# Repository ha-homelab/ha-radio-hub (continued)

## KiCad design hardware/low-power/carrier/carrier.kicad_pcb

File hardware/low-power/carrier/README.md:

# LP-C0 low-voltage module carrier

<!-- MC2-CURRENT-DESIGN -->
> **Current build: [MC2 — three external antennas](../../../docs/external-antennas.md).** This page retains an earlier design or evaluation for reference. Its board images, pin maps, enclosure fit and alternative BOMs are not the current MC2 build.

**This is a routed, electrically connected prototype PCB, not a production release.** The native KiCad 10 project includes a schematic, a two-layer PCB, a machine-readable connector map, assembly data and prototype Gerbers. The board passes native ERC, DRC, the unconnected-item check and schematic parity. It has not been fabricated, populated, powered or RF-tested. No radio pairing, PoE interoperability, long-run reliability or 3 W AC energy target is established by these CAD checks.

Open [carrier.kicad_pro](carrier.kicad_pro) in KiCad 10. The ready-to-review [schematic PDF](outputs/schematic.pdf), [assembly drawing](outputs/assembly-top.svg) and [top copper drawing](outputs/board-top.svg) are generated from the native files. The [validation summary](outputs/validation/summary.json) states the actual check results. [Prototype fabrication files](outputs/prototype-gerbers.zip) are for engineering review and a first article only.

## What this board does

LP-C0 is a **160 × 100 mm, 1.6 mm, two-layer low-voltage backplane**. SC16IS752, its 3.6864 MHz crystal, its TPS3808G33 reset supervisor, bypass capacitors, pull-ups and unused-input terminations are on the board. Radios, controller modules, the radar and the regulator are wired through keyed connectors. The CPU assignment remains the existing LP-P0 firmware contract: one S3 host, H2 Thread RCP, MG24 Zigbee NCP, ZAC93, CC1101, LD2450 and BME680.

The carrier contains no Ethernet magnetics or PoE primary circuitry. An independently reviewed isolated PoE front end supplies **regulated 5 V** at J1. A separately mounted Pololu D24V22F3 at J2 generates the sole 3.3 V rail. WIZ850io at J4 supplies the Ethernet controller, PHY, magnetics and RJ45. Do not connect raw PoE pairs or a 48 V source to this PCB.

This partition is useful for a bench build with accessible, replaceable modules. It is not a finished plug-together kit: the actual S3/H2 development-board revision must be checked for pin access, regulator backfeed and UART/LED conflicts. The included [LP-M0 daughterboard](mg24-adapter/README.md) provides the exact MGM240PA22VNA3 footprint, power/ground lands and service access. One populated M0 is required per C0 hub; its PCB, assembly and cable end must be included in procurement. No undocumented DevKit header, CC1101 header or radar connector footprint is claimed to fit.

## Connectors and harnesses

[connectors.json](connectors.json) is the complete pin-by-pin wiring list. It contains actual PCB pad centres, connector rotation, voltage domain, remote signal name and verified module-pad/header positions where available. [assembly-bom.csv](assembly-bom.csv) lists populated PCB parts; [harness-bom.csv](harness-bom.csv) lists the mating housings, contacts and off-board assembly items.

The board is viewed **from the component side**, with its origin at the upper-left corner and positive Y down. Every connector's square pad is pin 1. The J3 IDC header uses odd and even columns, not a single left-to-right sequence. A cable socket viewed into its mating face is mirrored relative to the PCB. Use moulded circuit numbers and the manufacturer drawing, then continuity-test every conductor. The pin numbers in this project belong to the **carrier connector**; they are not development-board header numbers. J3 is emphatically **not a Raspberry Pi header**.

- J1: 2-position JST XH, isolated 5 V input and return.
- J2: 3-position JST XH, buck VIN = fused 5 V, GND, buck VOUT = 3.3 V. Check this order before power.
- J3: 40-position keyed Würth IDC, S3 GPIO, duplicate 3.3 V and ground contacts. No 5 V.
- J4: 10-position JST XH, WIZ850io power and SPI. The official WIZ850io **J2.1 is GND; J2.2/3 are 3.3 V; J2.4 is NC**. The WIZ header J2 is distinct from carrier J2.
- J5: 7-position JST XH, H2 power, UART, EN and BOOT. EN/BOOT are open-drain controls with external pull-ups.
- J6: 6-position JST XH, MG24 power and UART with RTS/CTS.
- J7: 8-position JST XH, CC1101 power, SPI and GDO0/GDO2. GDO0 is shared open-drain TX with a 4.7 kΩ pull-up.
- J8: 5-position JST XH, ZAC93 3.3 V, both ground contacts and UART. SC16 TXA goes to ZAC93 RX; SC16 RXA receives ZAC93 TX.
- J9: 4-position JST XH, LD2450 5 V supply and 3.3 V UART. The radar is the only 5 V module on these peripheral harnesses.
- J10: JST SH STEMMA QT, 1 GND / 2 3.3 V / 3 SDA / 4 SCL. BME680 stays in a ventilated external pod. Its breakout provides the I²C pull-ups.

Use 22 AWG conductors on J1/J2 and 26 AWG on signal harnesses. The selected XH contact supports 28–22 AWG; the connector's 3 A rating is specified with 22 AWG. The selected IDC **mating socket is rated 1 A per contact**, regardless of the larger header rating. Keep SPI harnesses short: start at **100 mm maximum**, route a nearby ground return, and scope the actual edges before increasing length. This is a prototype layout constraint, not a measured signal-integrity guarantee. The 10 MHz W5500 and 4 MHz SC16 bus settings have not been validated through these cables.

## Module-side prerequisites

The required module-side wiring is described in [the LP-P0 hardware contract](../README.md). In particular:

1. Power S3/H2 modules only from the regulated 3.3 V rail after verifying that their development-board regulator and USB circuitry cannot backfeed it. Never connect another live 3.3 V supply. Isolate the S3 GPIO48 LED and UART0 USB bridge connections as required by the chosen board. Native S3 USB remains on GPIO19/20 and is not routed through J3.
2. H2 requires its documented GPIO8 pull-up and GPIO25 pull-down, EN timing and GPIO9 BOOT state. J5 does not expose those two strap pins; they must exist on the H2 module adapter. The carrier supplies EN/BOOT pull-ups and EN capacitance; account for any duplicate parts on a DevKit.
3. Use the included M0 adapter for MG24: its all-ground connection, VDD bypassing, antenna keepout, PA00 boot service, SWD PA01/PA02, reset and 3.3 V reference are part of the design. Connect C0 J6 to M0 J1 straight number-to-number. Do not add a 3.3 V pull-up to its reset pin. Flash the exact [MGM240P NCP build](../../../firmware/low-power/mg24/README.md), not an unrelated USB-dongle image.
4. ZAC93 and CC1101 connections terminate in harnesses because the physical revision and mounting dimensions of the user's boards are not verified. Check pin 1 and trace continuity at the actual board before attaching power.
5. The WIZ850io **data-only Ethernet RJ45 is not itself a PoE PD**. The separate verified front end must provide a data path and isolated 5 V; the carrier does not implement that external cable assembly.

## Power and assembly limits

F1 is Littelfuse **044901.5MR**, a 1.5 A time-delay fuse. It does not provide reverse-polarity protection, overvoltage protection or active current limiting. Use an isolated, current-limited 5 V source for first power. Start with only the external regulator, then measure J2.3 before connecting modules. The provisional continuous input criterion is **at most 1.0 A at 5 V**; re-evaluate the fuse and thermal derating against measured duty cycles. A fuse rating is not a measured current draw.

The shared 3.3 V rail uses a 0.8 mm routing class and a front copper pour; ground uses a rear pour. The SC16's small local supply escape is 0.25 mm. General signal traces are 0.25 mm, minimum clearance 0.20 mm, and routed vias are 0.8 mm with 0.4 mm drills. Copper is specified as 1 oz nominal per layer. Verify voltage at the furthest module during simultaneous radio activity; an unloaded 3.3 V reading is insufficient.

The PCB has hand-solderable 0805 passives, 1206 bulk capacitors, a TSSOP-28 UART bridge and SOT-23-6 supervisor. The JST SH connector is the finest-pitch part. Assemble low components first, inspect bridges under magnification, and measure resistance between rails before power. Three ground pads (J3.8, J4.2 and J4.9) have direct plane connections to avoid isolated thermal islands; they need more soldering heat or board preheat than the other connector pads.

The initial crystal load capacitors are 22 pF and 33 pF. Their values follow the existing design contract and remain a measured-frequency/drive-level gate. The crystal traces are short local front-layer routes reserved before global routing. Do not infer oscillator start-up margin from DRC. The SC16 64-byte receive FIFO still requires firmware stress testing with all radios active.

Mounting holes are 3.2 mm NPTH at **(5,5), (155,5), (5,95), (155,95) mm**. Use insulating M3 supports and protect the underside from conductive hardware. This hole pattern and the off-board harness layout **do not match the existing low-power enclosure mock-up**. Three support positions differ; do not print the old case expecting this board to fit. Harness bend radius, module antenna clearance, PoE isolation and BME/radar placement require an enclosure revision after a physical first article.

## Reproduce and verify

KiCad 10.0.6 was used locally. `generate.py` and `finalize.py` require the Python interpreter bundled with KiCad or a Python environment providing the matching `pcbnew`. The committed PCB is the routed result; regenerating only the schematic and placement does not recreate routing.

```sh
python3 generate.py --libraries /path/to/KiCad/SharedSupport
kicad-cli sch export netlist carrier.kicad_sch --format kicadxml -o .build/carrier.xml
java -jar /path/to/freerouting-1.9.0.jar -da -dct 0 -de .build/carrier.dsn -do .build/carrier.ses -mp 40 -mt 0
python3 finalize.py
python3 -m unittest test_contract -v
python3 validate.py --kicad-cli kicad-cli --out .build/validation
python3 export.py --kicad-cli kicad-cli
python3 validate.py --kicad-cli kicad-cli --check-hashes --out .build/recheck
```

Run from this directory. FreeRouting 1.9.0 needs a graphical display even in its command-line mode; a headless Linux reroute needs a virtual display. **CI does not need to reroute.** It checks the committed native PCB with KiCad and the independent netlist/connector validator. `-mt 0` avoids the old router's multithreaded optimization problems. `-da` disables its analytics. The intermediate DSN/SES and unrouted board live under ignored `.build/`.

Validation compares schematic-exported connectivity, native PCB pad nets and the canonical design; verifies all part positions/rotations, checks actual connector pad centres; and compares external endpoints against the independently sourced visual module atlas. Native DRC includes unconnected items and schematic parity. The script parses the JSON report as well as checking process status, because an observed KiCad CLI run returned success despite reporting errors.

No electrical violation is excluded. The reports list KiCad's default ignored non-electrical checks: missing courtyard (the four board-only mounting holes have no component courtyard), track-to-via centring, tuning geometries and unused symbol footprint filters/type metadata. There are no tuned differential pairs. The five explicitly unused SC16/supervisor output/control pins are marked with no-connect flags as required by the circuit; unused SC16 input/GPIO pins are terminated. See [NOTICE.md](NOTICE.md) for library provenance and licenses.

## Before a production order

Review the prototype Gerbers and drill map with the fabricator, then make a small first-article run. Inspect the pin-1 markings and connector fit before making cables. Validate the input fuse, rail droop, regulator temperature, oscillator frequency, reset/start-up sequence, SPI integrity, all radio traffic, antenna isolation, radar window and continuous operation. The off-board PoE front end and every module adapter need their own electrical/mechanical review. Production PCBA/test fixtures, enclosure design, RF/regulatory work and a saleable product release remain separate engineering steps.

The SHA256 manifest binds source files and exported artifacts, including the fabrication ZIP. Both C0 and M0 use descriptive `.gbr` Gerber filenames. J10 has two isolated solder hold-down tabs, represented as separate NC pins MP1/MP2; they are not extra cable contacts. The full named-pad check covers these tabs as well as numbered electrical pads.

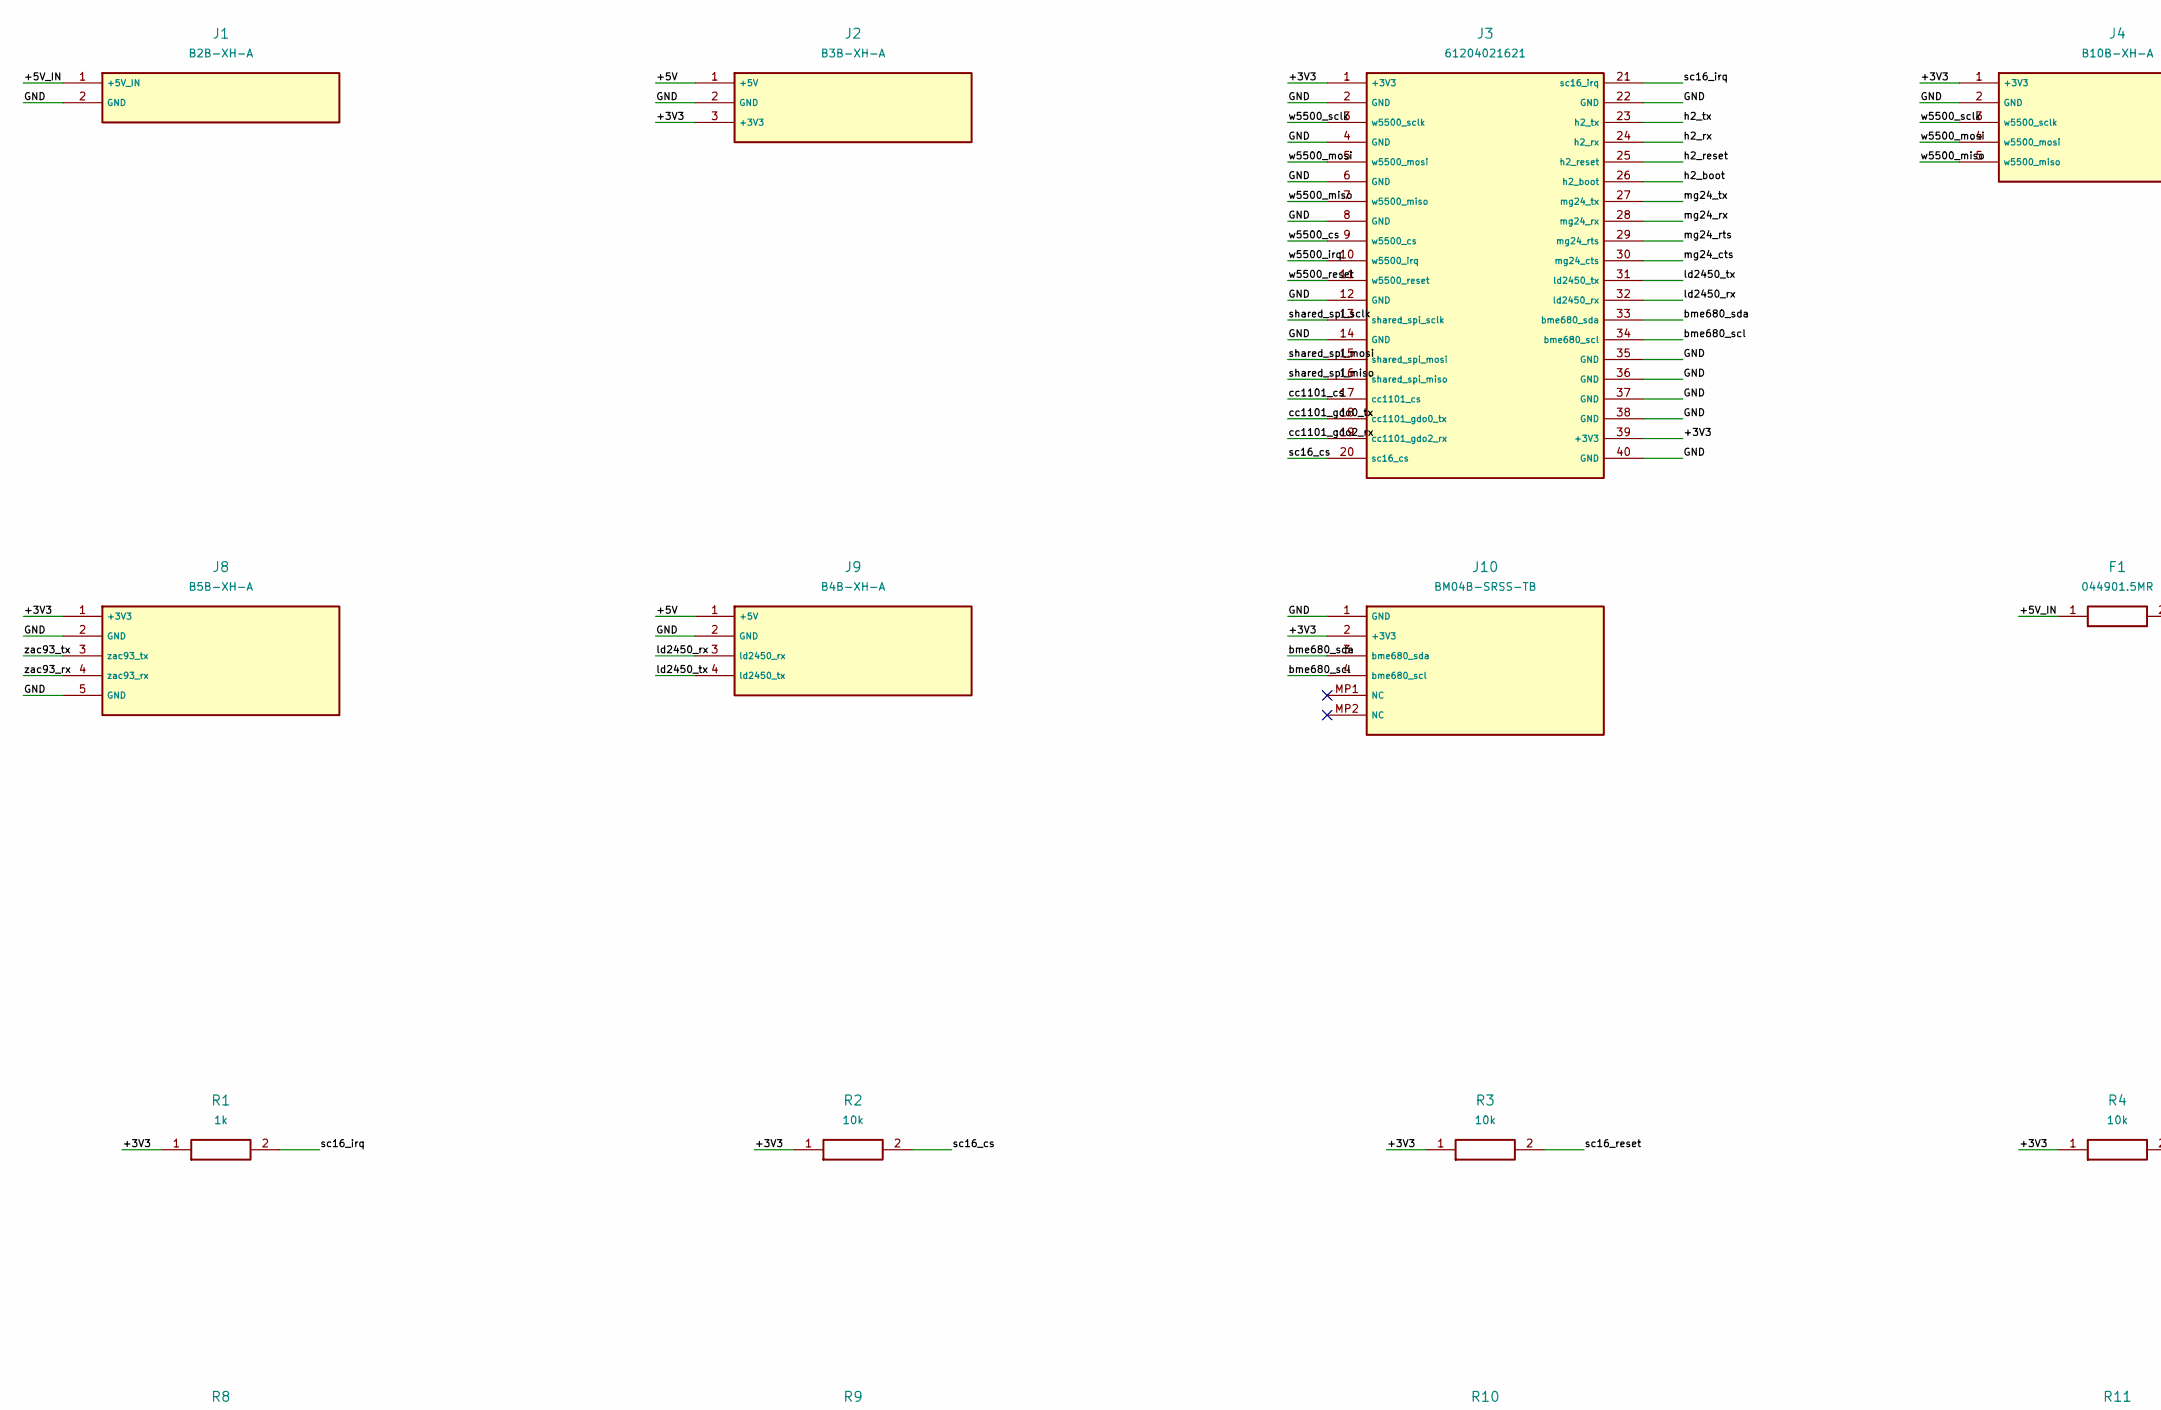
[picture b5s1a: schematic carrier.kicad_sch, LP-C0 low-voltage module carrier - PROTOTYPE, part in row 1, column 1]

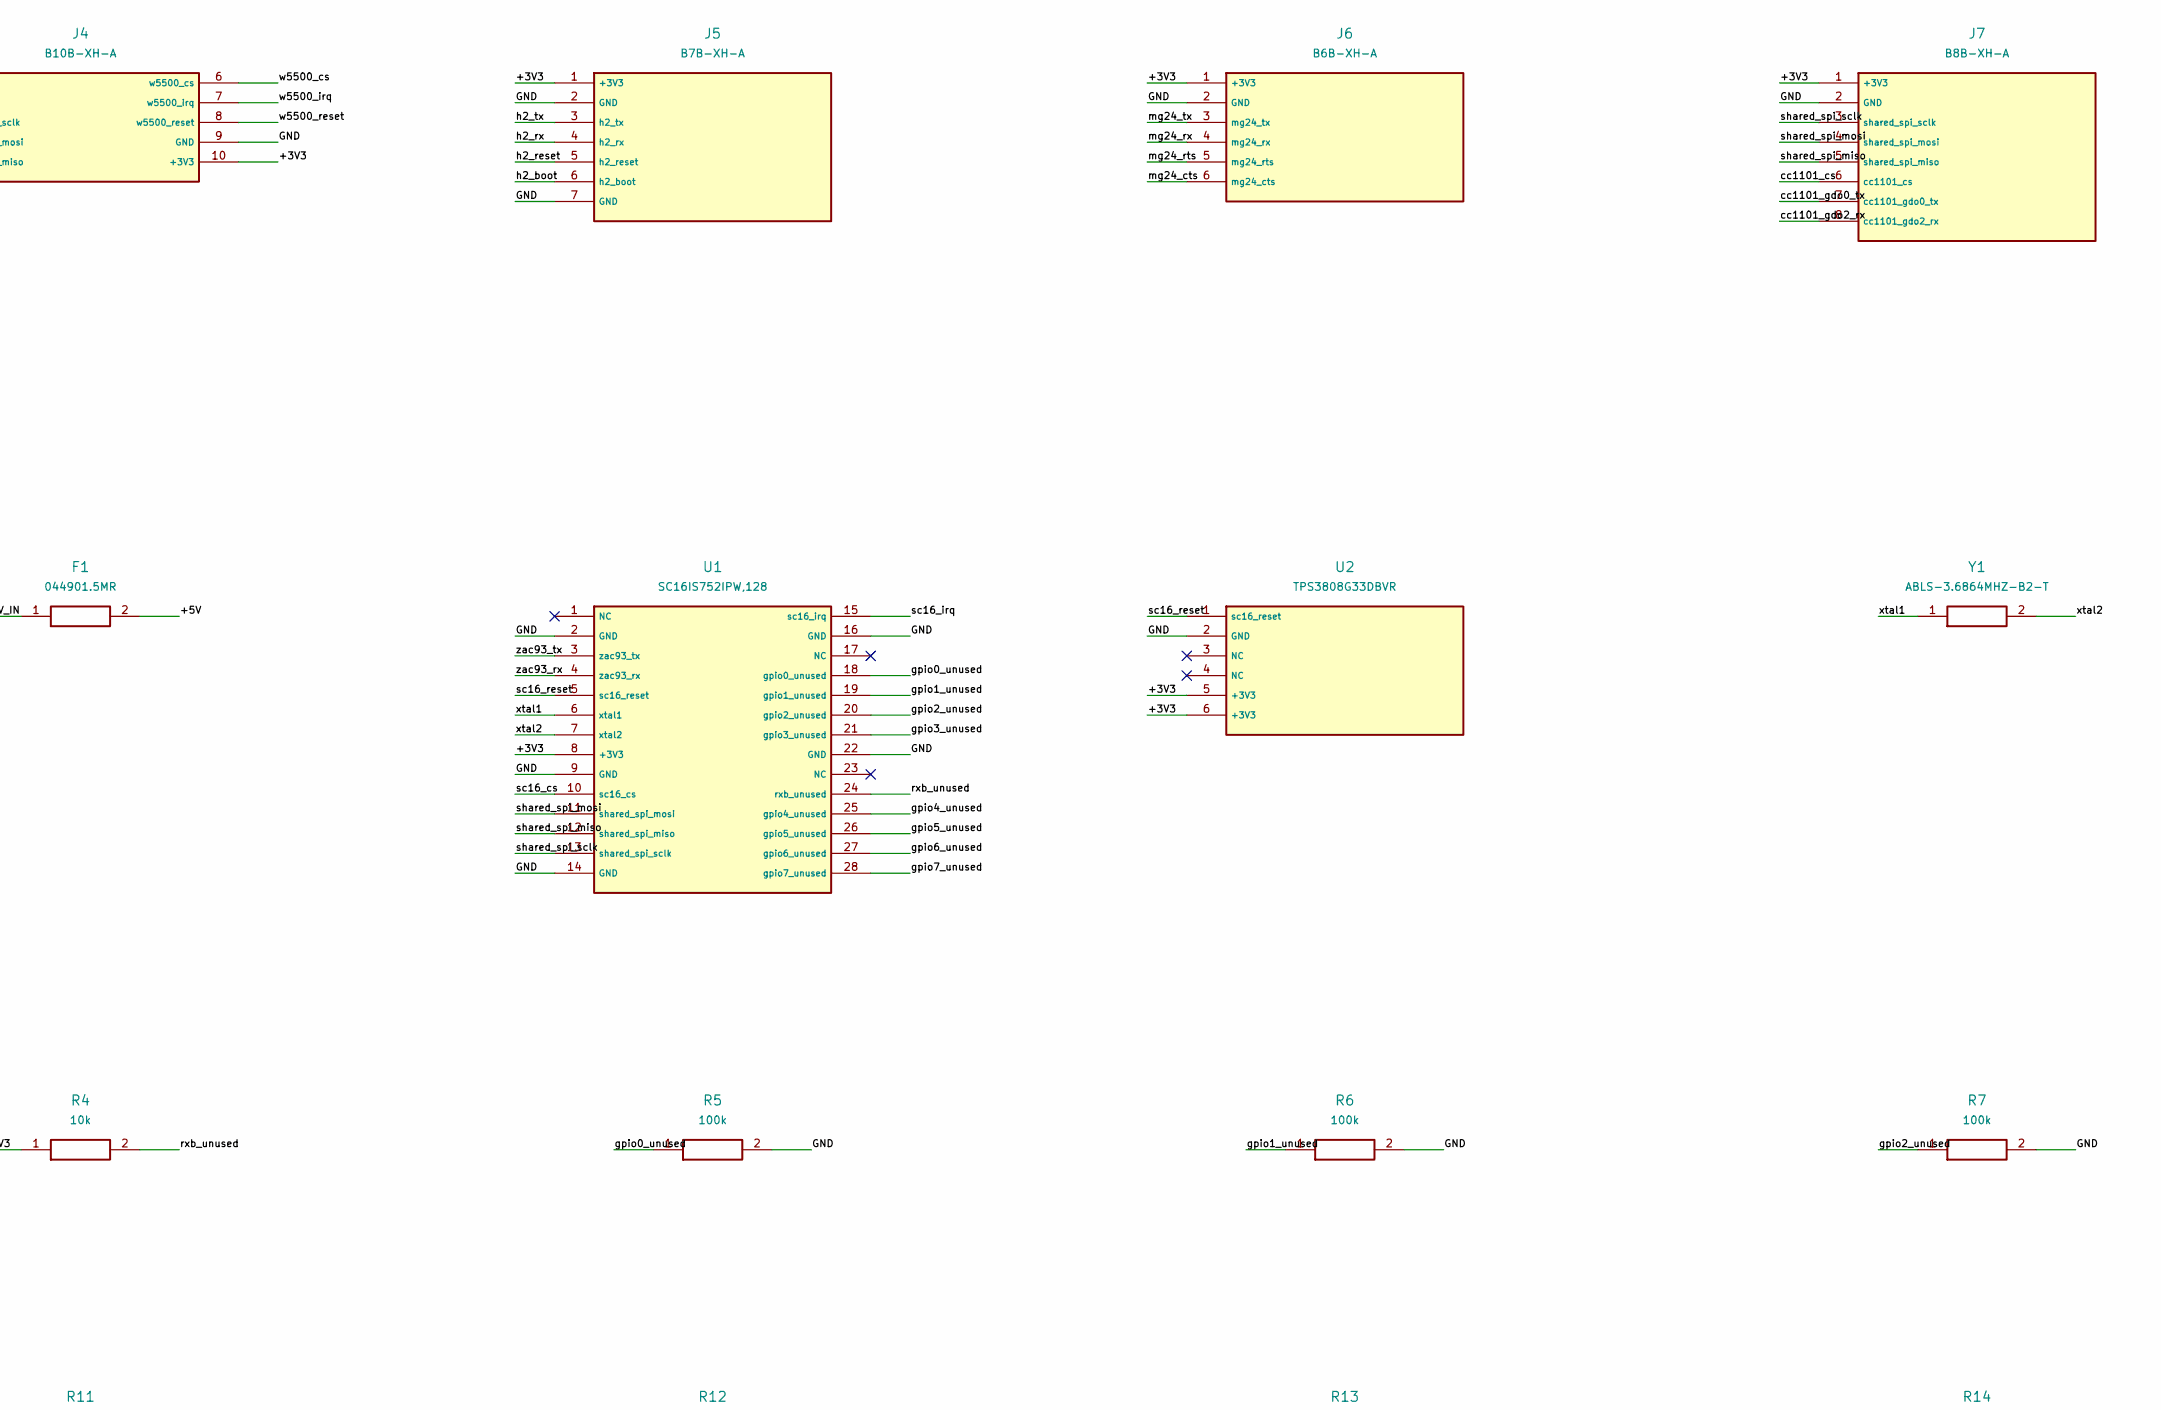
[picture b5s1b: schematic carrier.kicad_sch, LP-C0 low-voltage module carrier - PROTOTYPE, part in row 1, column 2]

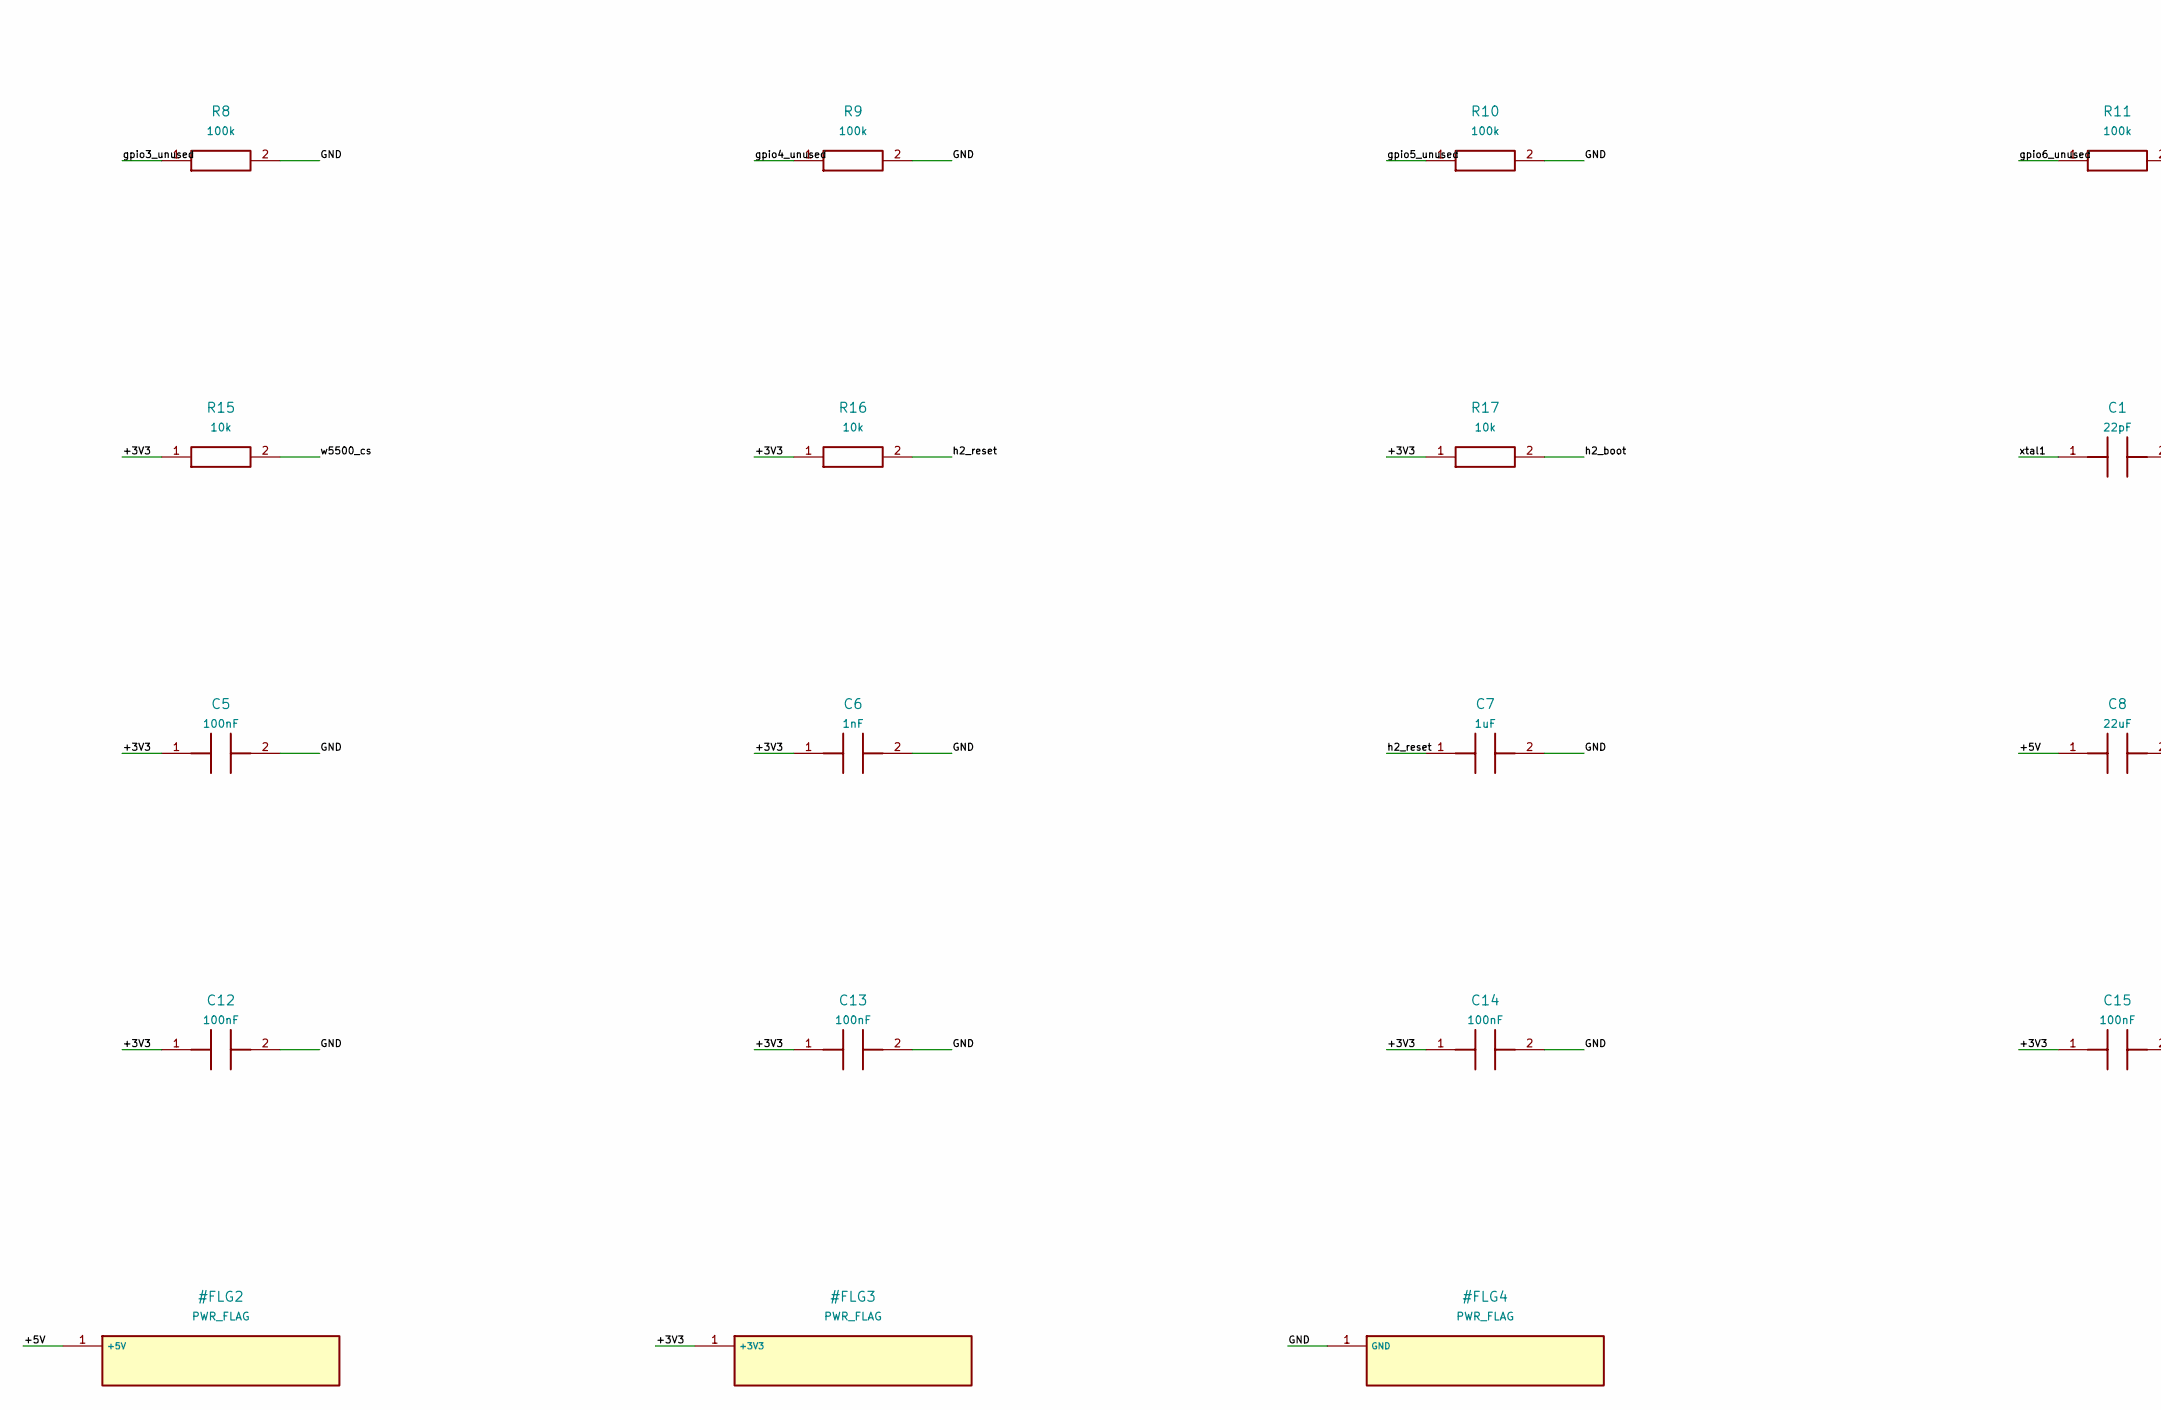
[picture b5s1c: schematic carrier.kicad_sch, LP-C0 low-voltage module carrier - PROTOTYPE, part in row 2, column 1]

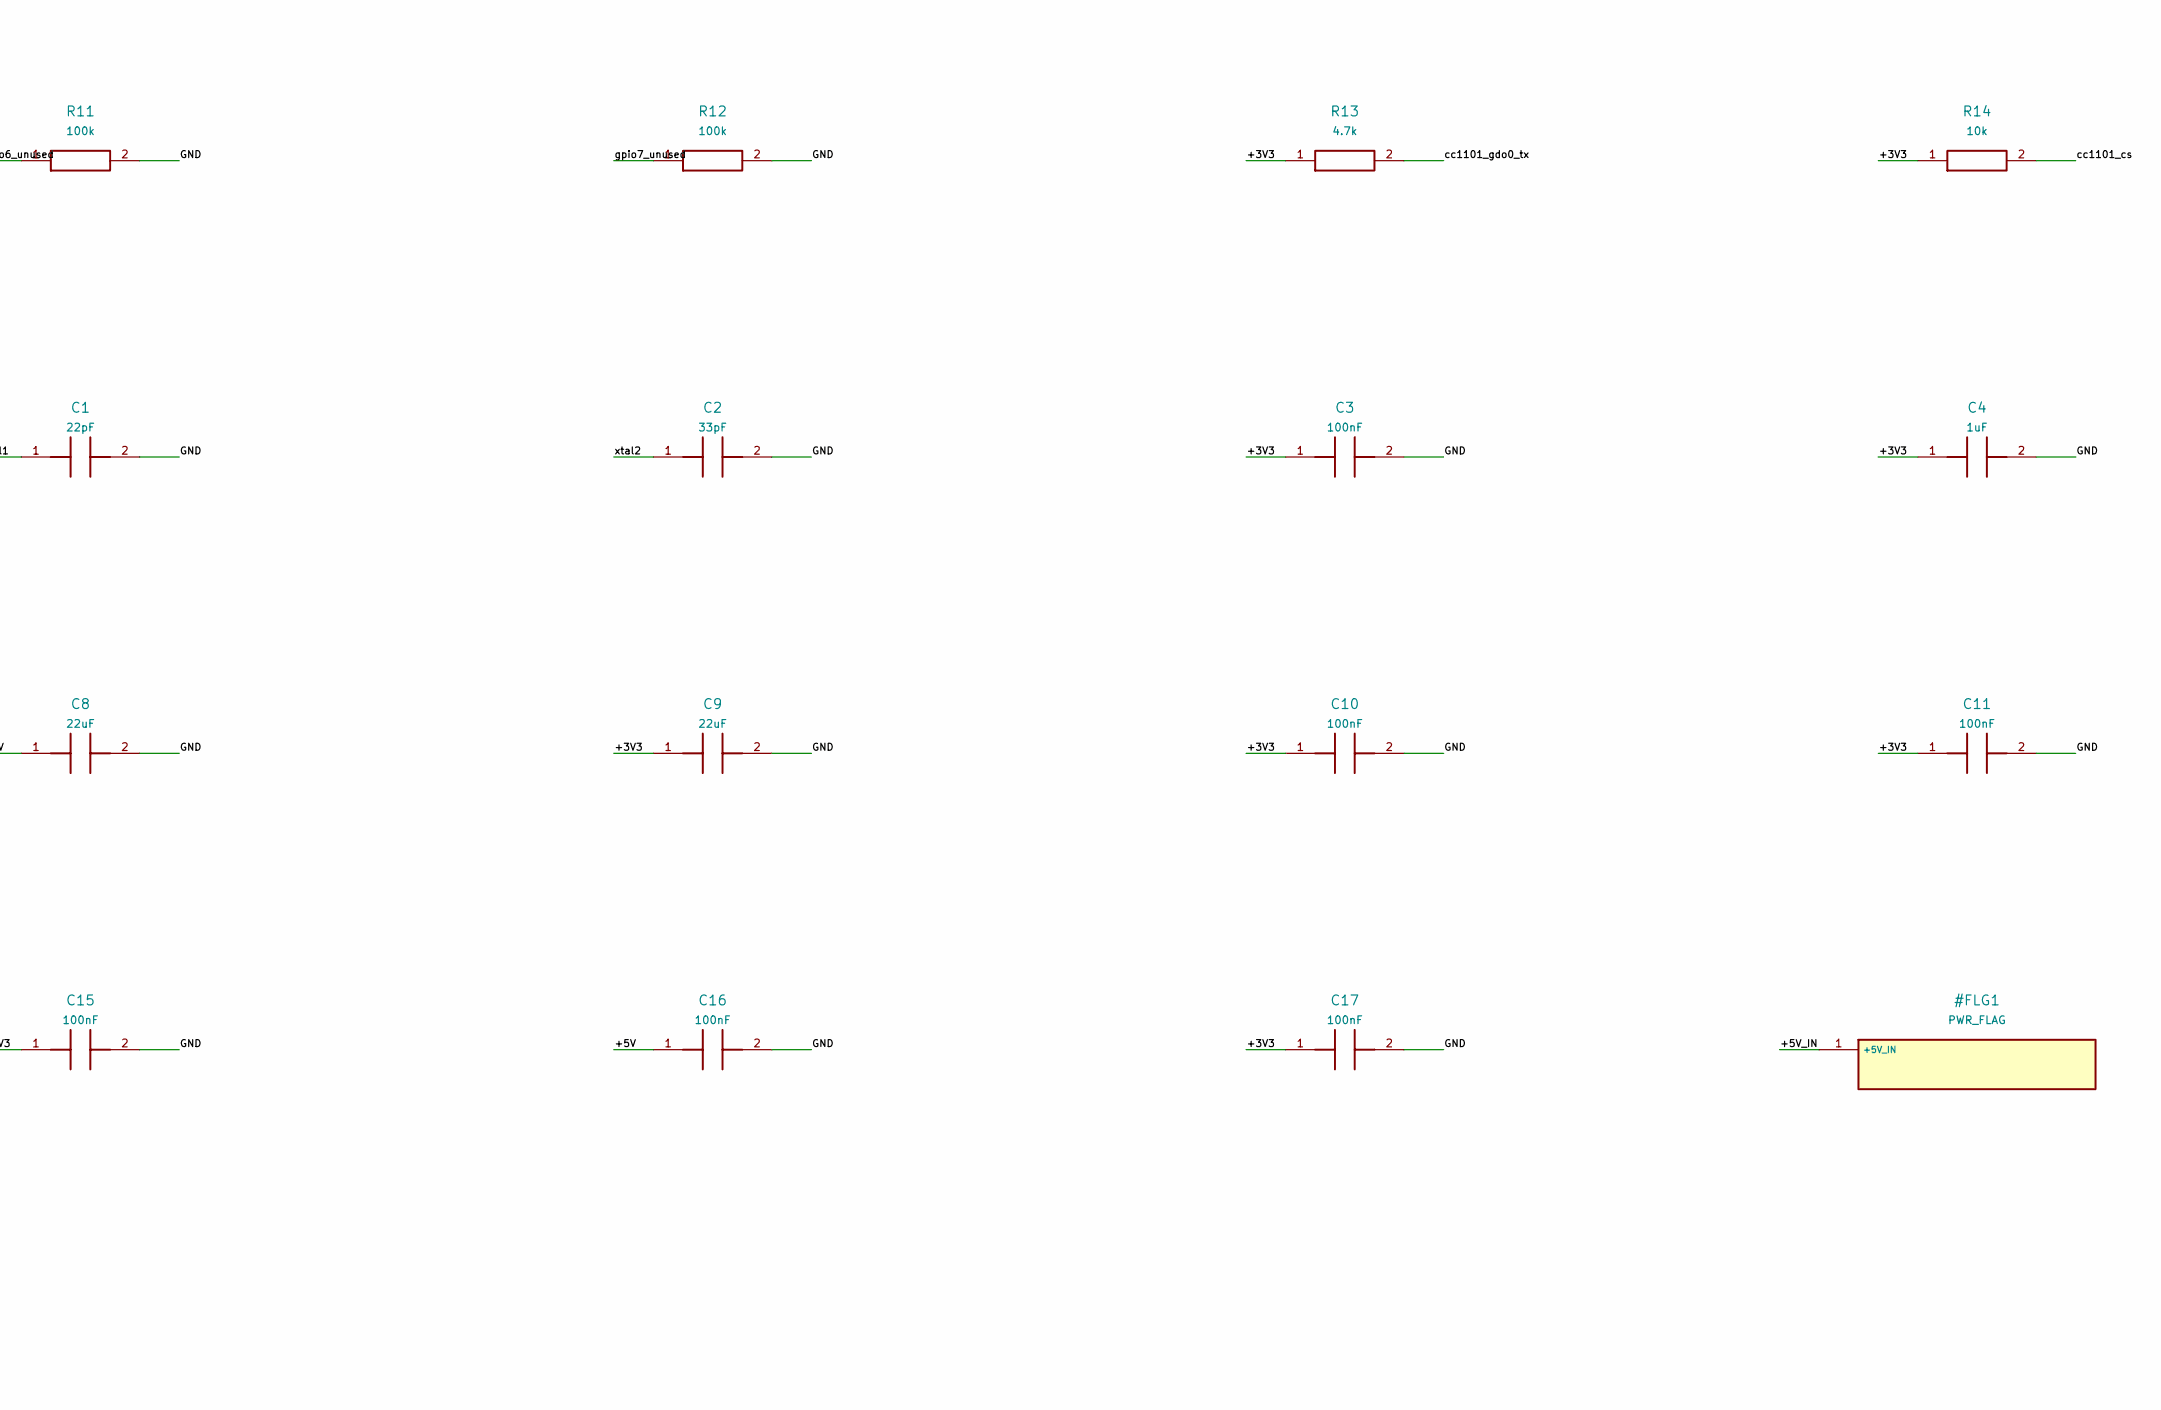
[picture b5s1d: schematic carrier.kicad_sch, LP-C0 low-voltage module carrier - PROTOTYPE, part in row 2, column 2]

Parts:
C1: 22pF; C_0805_2012Metric
C2: 33pF; C_0805_2012Metric
C3, C5, C10, C11, C12, C13, C14, C15, C16, C17: 100nF; C_0805_2012Metric
C4, C7: 1uF; C_0805_2012Metric
C6: 1nF; C_0805_2012Metric
C8, C9: 22uF; C_1206_3216Metric
F1: 044901.5MR; Littelfuse_449
J1: B2B-XH-A; JST_XH_B2B-XH-A_1x02_P2.50mm_Vertical
J2: B3B-XH-A; JST_XH_B3B-XH-A_1x03_P2.50mm_Vertical
J3: 61204021621; Wurth_61204021621
J4: B10B-XH-A; JST_XH_B10B-XH-A_1x10_P2.50mm_Vertical
J5: B7B-XH-A; JST_XH_B7B-XH-A_1x07_P2.50mm_Vertical
J6: B6B-XH-A; JST_XH_B6B-XH-A_1x06_P2.50mm_Vertical
J7: B8B-XH-A; JST_XH_B8B-XH-A_1x08_P2.50mm_Vertical
J8: B5B-XH-A; JST_XH_B5B-XH-A_1x05_P2.50mm_Vertical
J9: B4B-XH-A; JST_XH_B4B-XH-A_1x04_P2.50mm_Vertical
J10: BM04B-SRSS-TB; JST_SH_BM04B-SRSS-TB_1x04-1MP_P1.00mm_Vertical
R1: 1k; R_0805_2012Metric
R2, R3, R4, R14, R15, R16, R17: 10k; R_0805_2012Metric
R5, R6, R7, R8, R9, R10, R11, R12: 100k; R_0805_2012Metric
R13: 4.7k; R_0805_2012Metric
U1: SC16IS752IPW,128; TSSOP-28_4.4x9.7mm_P0.65mm
U2: TPS3808G33DBVR; SOT-23-6
Y1: ABLS-3.6864MHZ-B2-T; Crystal_SMD_HC49-SD

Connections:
/+3V3: C3.1, C4.1, C5.1, C6.1, C9.1, C10.1, C11.1, C12.1, C13.1, C14.1, C15.1, C17.1, J2.3 (+3V3), J3.1 (+3V3), J3.39 (+3V3), J4.1 (+3V3), J4.10 (+3V3), J5.1 (+3V3), J6.1 (+3V3), J7.1 (+3V3), J8.1 (+3V3), J10.2 (+3V3), R1.1, R2.1, R3.1, R4.1, R13.1, R14.1, R15.1, R16.1, R17.1, U1.8 (+3V3), U2.5 (+3V3), U2.6 (+3V3)
/+5V: C8.1, C16.1, F1.2, J2.1 (+5V), J9.1 (+5V)
/+5V_IN: F1.1, J1.1 (+5V_IN)
/GND: C1.2, C2.2, C3.2, C4.2, C5.2, C6.2, C7.2, C8.2, C9.2, C10.2, C11.2, C12.2, C13.2, C14.2, C15.2, C16.2, C17.2, J1.2 (GND), J2.2 (GND), J3.2 (GND), J3.4 (GND), J3.6 (GND), J3.8 (GND), J3.12 (GND), J3.14 (GND), J3.22 (GND), J3.35 (GND), J3.36 (GND), J3.37 (GND), J3.38 (GND), J3.40 (GND), J4.2 (GND), J4.9 (GND), J5.2 (GND), J5.7 (GND), J6.2 (GND), J7.2 (GND), J8.2 (GND), J8.5 (GND), J9.2 (GND), J10.1 (GND), R5.2, R6.2, R7.2, R8.2, R9.2, R10.2, R11.2, R12.2, U1.2 (GND), U1.9 (GND), U1.14 (GND), U1.16 (GND), U1.22 (GND), U2.2 (GND)
/bme680_scl: J3.34 (bme680_scl), J10.4 (bme680_scl)
/bme680_sda: J3.33 (bme680_sda), J10.3 (bme680_sda)
/cc1101_cs: J3.17 (cc1101_cs), J7.6 (cc1101_cs), R14.2
/cc1101_gdo0_tx: J3.18 (cc1101_gdo0_tx), J7.7 (cc1101_gdo0_tx), R13.2
/cc1101_gdo2_rx: J3.19 (cc1101_gdo2_rx), J7.8 (cc1101_gdo2_rx)
/gpio0_unused: R5.1, U1.18 (gpio0_unused)
/gpio1_unused: R6.1, U1.19 (gpio1_unused)
/gpio2_unused: R7.1, U1.20 (gpio2_unused)
/gpio3_unused: R8.1, U1.21 (gpio3_unused)
/gpio4_unused: R9.1, U1.25 (gpio4_unused)
/gpio5_unused: R10.1, U1.26 (gpio5_unused)
/gpio6_unused: R11.1, U1.27 (gpio6_unused)
/gpio7_unused: R12.1, U1.28 (gpio7_unused)
/h2_boot: J3.26 (h2_boot), J5.6 (h2_boot), R17.2
/h2_reset: C7.1, J3.25 (h2_reset), J5.5 (h2_reset), R16.2
/h2_rx: J3.24 (h2_rx), J5.4 (h2_rx)
/h2_tx: J3.23 (h2_tx), J5.3 (h2_tx)
/ld2450_rx: J3.32 (ld2450_rx), J9.3 (ld2450_rx)
/ld2450_tx: J3.31 (ld2450_tx), J9.4 (ld2450_tx)
/mg24_cts: J3.30 (mg24_cts), J6.6 (mg24_cts)
/mg24_rts: J3.29 (mg24_rts), J6.5 (mg24_rts)
/mg24_rx: J3.28 (mg24_rx), J6.4 (mg24_rx)
/mg24_tx: J3.27 (mg24_tx), J6.3 (mg24_tx)
/rxb_unused: R4.2, U1.24 (rxb_unused)
/sc16_cs: J3.20 (sc16_cs), R2.2, U1.10 (sc16_cs)
/sc16_irq: J3.21 (sc16_irq), R1.2, U1.15 (sc16_irq)
/sc16_reset: R3.2, U1.5 (sc16_reset), U2.1 (sc16_reset)
/shared_spi_miso: J3.16 (shared_spi_miso), J7.5 (shared_spi_miso), U1.12 (shared_spi_miso)
/shared_spi_mosi: J3.15 (shared_spi_mosi), J7.4 (shared_spi_mosi), U1.11 (shared_spi_mosi)
/shared_spi_sclk: J3.13 (shared_spi_sclk), J7.3 (shared_spi_sclk), U1.13 (shared_spi_sclk)
/w5500_cs: J3.9 (w5500_cs), J4.6 (w5500_cs), R15.2
/w5500_irq: J3.10 (w5500_irq), J4.7 (w5500_irq)
/w5500_miso: J3.7 (w5500_miso), J4.5 (w5500_miso)
/w5500_mosi: J3.5 (w5500_mosi), J4.4 (w5500_mosi)
/w5500_reset: J3.11 (w5500_reset), J4.8 (w5500_reset)
/w5500_sclk: J3.3 (w5500_sclk), J4.3 (w5500_sclk)
/xtal1: C1.1, U1.6 (xtal1), Y1.1
/xtal2: C2.1, U1.7 (xtal2), Y1.2
/zac93_rx: J8.4 (zac93_rx), U1.4 (zac93_rx)
/zac93_tx: J8.3 (zac93_tx), U1.3 (zac93_tx)

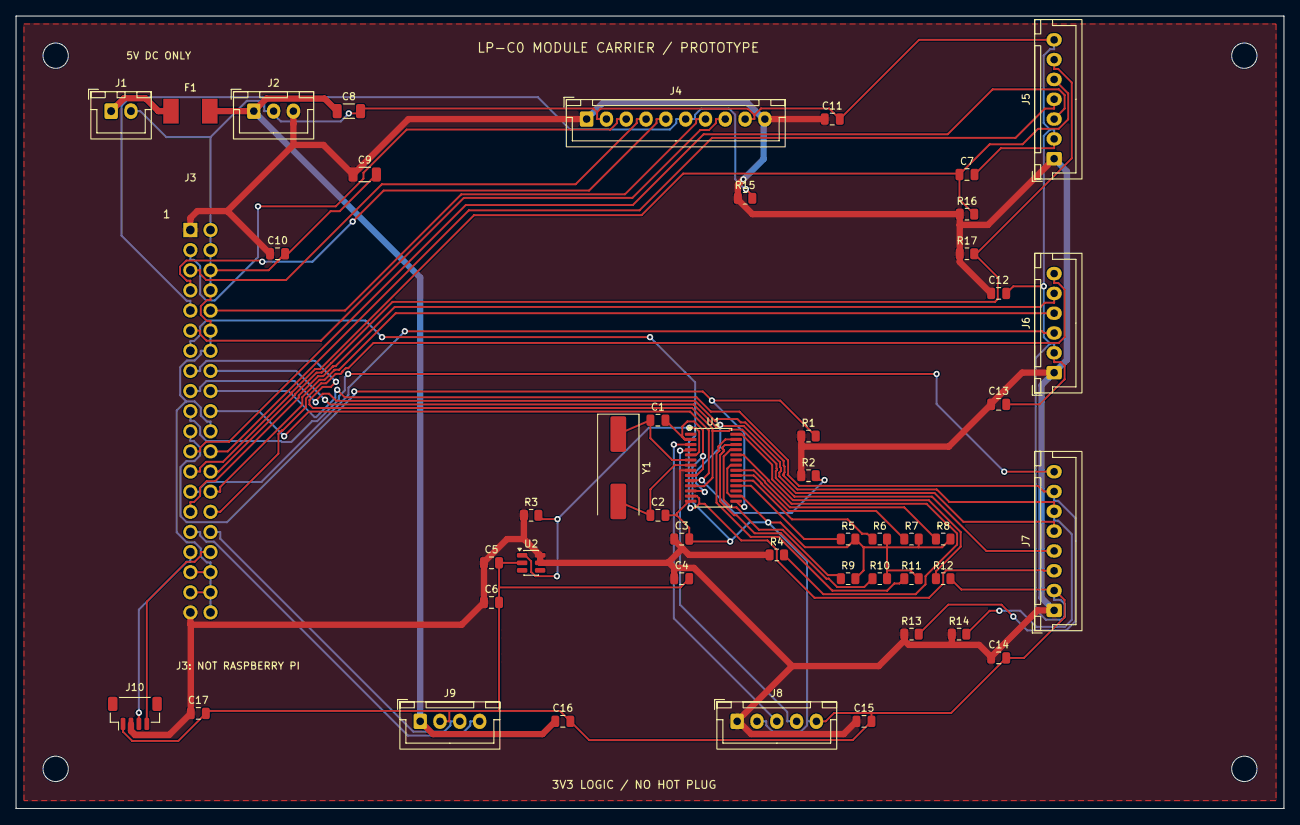
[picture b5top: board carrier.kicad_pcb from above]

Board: 2 copper layers, 160.0 x 100.0 mm, 52 parts (0 on the bottom side), 44 nets.

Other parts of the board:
H1, H2, H3, H4: M3 NPTH

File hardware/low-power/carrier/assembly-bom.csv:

Reference,Quantity,Manufacturer part / value,Footprint,Note,Source
J1,1,B2B-XH-A,Carrier:JST_XH_B2B-XH-A_1x02_P2.50mm_Vertical,Isolated regulated 5V input,https://www.jst-mfg.com/product/pdf/eng/eXH.pdf
J2,1,B3B-XH-A,Carrier:JST_XH_B3B-XH-A_1x03_P2.50mm_Vertical,External D24V22F3 buck,https://www.jst-mfg.com/product/pdf/eng/eXH.pdf
J3,1,61204021621,Carrier:Wurth_61204021621,S3 keyed 40-position IDC harness; NOT Raspberry Pi compatible,https://www.we-online.com/components/products/datasheet/6120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
J4,1,B10B-XH-A,Carrier:JST_XH_B10B-XH-A_1x10_P2.50mm_Vertical,WIZ850io Ethernet module,https://www.jst-mfg.com/product/pdf/eng/eXH.pdf
J5,1,B7B-XH-A,Carrier:JST_XH_B7B-XH-A_1x07_P2.50mm_Vertical,H2 Thread RCP,https://www.jst-mfg.com/product/pdf/eng/eXH.pdf
J6,1,B6B-XH-A,Carrier:JST_XH_B6B-XH-A_1x06_P2.50mm_Vertical,MG24 Zigbee NCP,https://www.jst-mfg.com/product/pdf/eng/eXH.pdf
J7,1,B8B-XH-A,Carrier:JST_XH_B8B-XH-A_1x08_P2.50mm_Vertical,CC1101 RF module,https://www.jst-mfg.com/product/pdf/eng/eXH.pdf
J8,1,B5B-XH-A,Carrier:JST_XH_B5B-XH-A_1x05_P2.50mm_Vertical,ZAC93 Z-Wave module,https://www.jst-mfg.com/product/pdf/eng/eXH.pdf
J9,1,B4B-XH-A,Carrier:JST_XH_B4B-XH-A_1x04_P2.50mm_Vertical,LD2450 radar,https://www.jst-mfg.com/product/pdf/eng/eXH.pdf
J10,1,BM04B-SRSS-TB,Carrier:JST_SH_BM04B-SRSS-TB_1x04-1MP_P1.00mm_Vertical,STEMMA QT: 3.3V only; BME680 external ventilated pod,https://www.jst-mfg.com/product/pdf/eng/eSH.pdf
F1,1,044901.5MR,Carrier:Littelfuse_449,"1.5A time-delay; design <=1.0A continuous at 5V, temperature derating applies",https://www.littelfuse.com/assetdocs/fuses-449-datasheet?ass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
U1,1,"SC16IS752IPW,128",Carrier:TSSOP-28_4.4x9.7mm_P0.65mm,"SPI mode; channel A 115200 8N1, crystal3.6864MHz",https://www.nxp.com/docs/en/data-sheet/SC16IS752_SC16IS762.pdf
U2,1,TPS3808G33DBVR,Carrier:SOT-23-6,G33 supervisor; CT open=20ms; MR internal pullup,https://www.ti.com/lit/ds/symlink/tps3808.pdf
Y1,1,ABLS-3.6864MHZ-B2-T,Carrier:Crystal_SMD_HC49-SD,"18pF CL, initial load caps22pF/33pF; verify frequency/drive on bench",https://abracon.com/Resonators/abls.pdf
R1,1,1k,Carrier:R_0805_2012Metric,"1%, 0.125W, 0805; select a stocked part meeting these specifications",
R2,1,10k,Carrier:R_0805_2012Metric,"1%, 0.125W, 0805; select a stocked part meeting these specifications",
R3,1,10k,Carrier:R_0805_2012Metric,"1%, 0.125W, 0805; select a stocked part meeting these specifications",
R4,1,10k,Carrier:R_0805_2012Metric,"1%, 0.125W, 0805; select a stocked part meeting these specifications",
R5,1,100k,Carrier:R_0805_2012Metric,"1%, 0.125W, 0805; select a stocked part meeting these specifications",
R6,1,100k,Carrier:R_0805_2012Metric,"1%, 0.125W, 0805; select a stocked part meeting these specifications",
R7,1,100k,Carrier:R_0805_2012Metric,"1%, 0.125W, 0805; select a stocked part meeting these specifications",
R8,1,100k,Carrier:R_0805_2012Metric,"1%, 0.125W, 0805; select a stocked part meeting these specifications",
R9,1,100k,Carrier:R_0805_2012Metric,"1%, 0.125W, 0805; select a stocked part meeting these specifications",
R10,1,100k,Carrier:R_0805_2012Metric,"1%, 0.125W, 0805; select a stocked part meeting these specifications",
R11,1,100k,Carrier:R_0805_2012Metric,"1%, 0.125W, 0805; select a stocked part meeting these specifications",
R12,1,100k,Carrier:R_0805_2012Metric,"1%, 0.125W, 0805; select a stocked part meeting these specifications",
R13,1,4.7k,Carrier:R_0805_2012Metric,"1%, 0.125W, 0805; select a stocked part meeting these specifications",
R14,1,10k,Carrier:R_0805_2012Metric,"1%, 0.125W, 0805; select a stocked part meeting these specifications",
R15,1,10k,Carrier:R_0805_2012Metric,"1%, 0.125W, 0805; select a stocked part meeting these specifications",
R16,1,10k,Carrier:R_0805_2012Metric,"1%, 0.125W, 0805; select a stocked part meeting these specifications",
R17,1,10k,Carrier:R_0805_2012Metric,"1%, 0.125W, 0805; select a stocked part meeting these specifications",
C1,1,22pF,Carrier:C_0805_2012Metric,"10V minimum; C0G crystal caps, X7R bypass/bulk",
C2,1,33pF,Carrier:C_0805_2012Metric,"10V minimum; C0G crystal caps, X7R bypass/bulk",
C3,1,100nF,Carrier:C_0805_2012Metric,"10V minimum; C0G crystal caps, X7R bypass/bulk",
C4,1,1uF,Carrier:C_0805_2012Metric,"10V minimum; C0G crystal caps, X7R bypass/bulk",
C5,1,100nF,Carrier:C_0805_2012Metric,"10V minimum; C0G crystal caps, X7R bypass/bulk",
C6,1,1nF,Carrier:C_0805_2012Metric,"10V minimum; C0G crystal caps, X7R bypass/bulk",
C7,1,1uF,Carrier:C_0805_2012Metric,"10V minimum; C0G crystal caps, X7R bypass/bulk",
C8,1,22uF,Carrier:C_1206_3216Metric,"10V minimum; C0G crystal caps, X7R bypass/bulk",
C9,1,22uF,Carrier:C_1206_3216Metric,"10V minimum; C0G crystal caps, X7R bypass/bulk",
C10,1,100nF,Carrier:C_0805_2012Metric,"10V minimum; C0G crystal caps, X7R bypass/bulk",
C11,1,100nF,Carrier:C_0805_2012Metric,"10V minimum; C0G crystal caps, X7R bypass/bulk",
C12,1,100nF,Carrier:C_0805_2012Metric,"10V minimum; C0G crystal caps, X7R bypass/bulk",
C13,1,100nF,Carrier:C_0805_2012Metric,"10V minimum; C0G crystal caps, X7R bypass/bulk",
C14,1,100nF,Carrier:C_0805_2012Metric,"10V minimum; C0G crystal caps, X7R bypass/bulk",
C15,1,100nF,Carrier:C_0805_2012Metric,"10V minimum; C0G crystal caps, X7R bypass/bulk",
C16,1,100nF,Carrier:C_0805_2012Metric,"10V minimum; C0G crystal caps, X7R bypass/bulk",
C17,1,100nF,Carrier:C_0805_2012Metric,"10V minimum; C0G crystal caps, X7R bypass/bulk",
